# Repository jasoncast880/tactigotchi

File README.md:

🚀 Project Title

A handheld system based on the Raspberry Pi Pico W
📦 Overview

This project features:

    Custom hardware using RP2040

    Firmware written in C/C++ using GCC & Pico SDK

    Support for SPI LCD Display & SD Card, I2C Buttons, Wi-Fi, BLE, DMA Data Transfer (PIO is WIP)

🔧 Hardware
Microcontroller

    Board: [e.g., Raspberry Pi Pico / STM32F401 / ESP32]

    Processor: [e.g., ARM Cortex-M0+ @ 133MHz]

Schematic & PCB <br>
MCU Schematic:<br>
<br>
PSU:<br>
<br>
LCD/SDC THT Module:<br>
<br>
Speaker && IR Emitter Modules:<br>
<br>

    [Link to schematic or image]

    [Link to PCB files or KiCad/Altium project]

🧠 Firmware
Features

[Feature 1 – e.g., Sensor reading with ADC]

[Feature 2 – e.g., Wi-Fi transmission]

    [Planned Feature – e.g., OTA firmware update]

Toolchain

    Language: C/C++

    Build System: CMake

    RTOS: FreeRTOS

    SDK: Raspberry Pi Pico SDK v1.5.1 (update)

Directory Structure (update...)

project/
├── hardware/         # Schematics, PCB design files
├── pockpet/
└── README.md

🚀 Getting Started
Requirements

    Compiler/toolchain: arm-none-eabi-gcc

    A 'Tactigotchi' official hardware kit!

Building the Firmware

git clone https://github.com/yourusername/project.git
cd project
mkdir build && cd build
cmake ..
make

Flashing to Device

# Example for Raspberry Pi Pico (drag-and-drop)
cp firmware.uf2 /media/PI-PICO/

Or, using OpenOCD / pyOCD:

openocd -f interface/cmsis-dap.cfg -f target/rp2040.cfg

📈 Performance & Testing

    Power consumption: [value]

    Real-time responsiveness: [value / approach used]

    Debugging methods: [e.g., UART, SWD, printf-style logging]

🗂️ Documentation

    [Link to datasheets, application notes, or online documentation]

    [Optional: Link to a GitHub Wiki or Doxygen-generated docs]

🧪 Development Notes

    Known Issues: [List any bugs or limitations]

    Future Work: [Planned improvements or extensions]

    Contributions: [Mention if pull requests/issues are welcome]

📜 License

[MIT / GPL / Apache 2.0 / etc.]
🙌 Acknowledgments

    [Any libraries or codebases used]

    [Contributors, inspirations, mentors]

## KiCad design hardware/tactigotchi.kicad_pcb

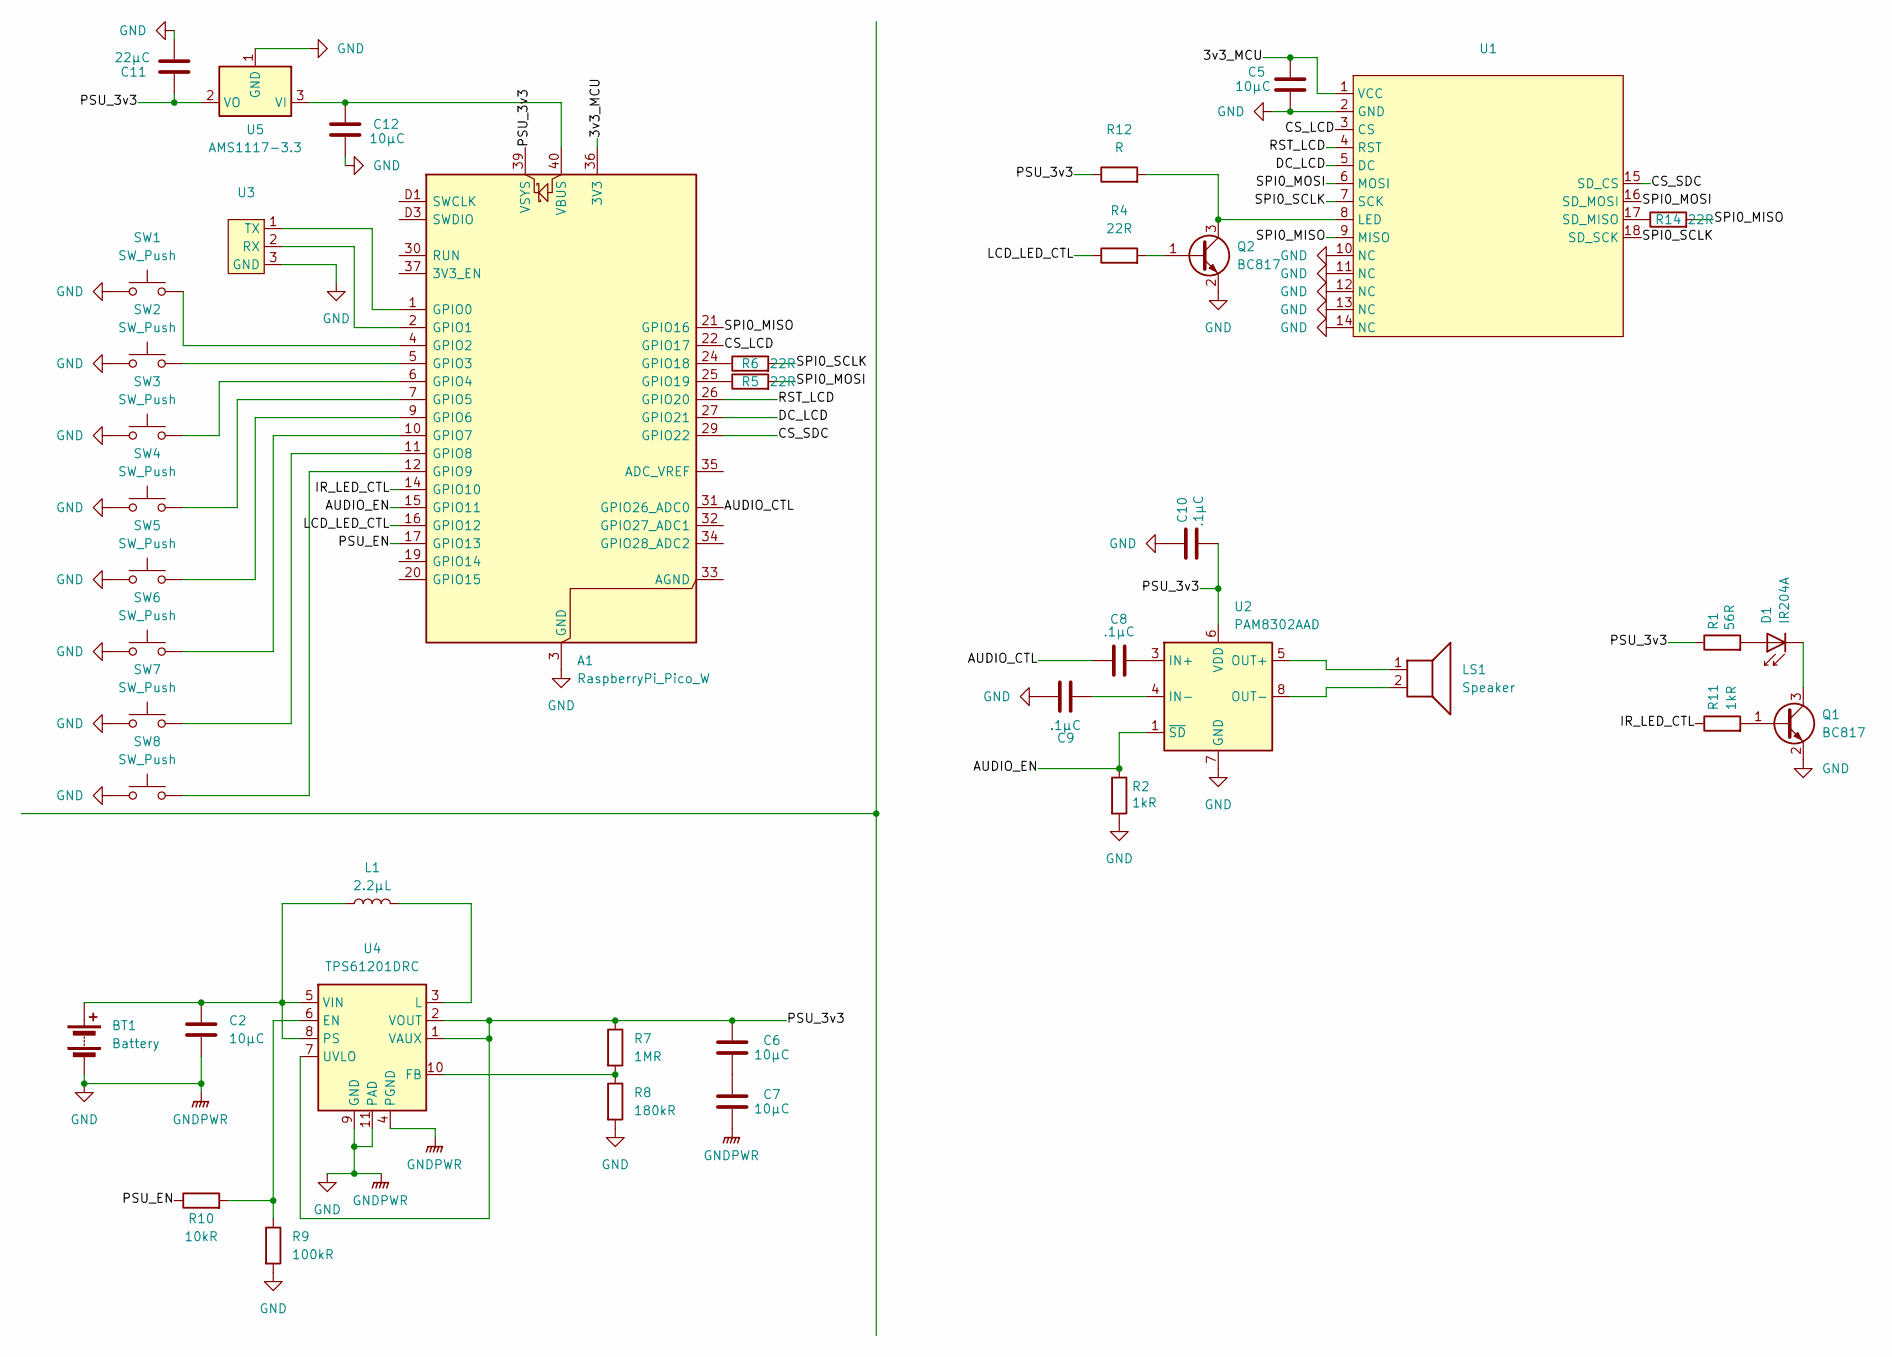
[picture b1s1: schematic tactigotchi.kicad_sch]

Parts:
A1: RaspberryPi_Pico_W; RaspberryPi_Pico_W_SMD_HandSolder
BT1: Battery; PinHeader_1x02_P1.27mm_Vertical
C2, C5, C6, C7, C12: 10μC; C_1206_3216Metric
C8, C9, C10: .1μC; C_1206_3216Metric
C11: 22μC; C_1206_3216Metric
D1: IR204A; LED_D3.0mm_IRBlack
L1: 2.2μL; L_1206_3216Metric
LS1: Speaker; Buzzer_12x9.5RM7.6
Q1, Q2: BC817; SOT-23
R1: 56R; R_1206_3216Metric
R2, R11: 1kR; R_1206_3216Metric
R4, R5, R6, R14: 22R; R_1206_3216Metric
R7: 1MR; R_1206_3216Metric
R8: 180kR; R_1206_3216Metric
R9: 100kR; R_1206_3216Metric
R10: 10kR; R_1206_3216Metric
R12: R; R_1206_3216Metric
SW1, SW2, SW3, SW4, SW5, SW6, SW7, SW8: SW_Push; SW_SPST_PTS645
U1: ILI9341_Module
U2: PAM8302AAD; SOIC-8-1EP_3.9x4.9mm_P1.27mm_EP2.41x3.3mm
U3: 3x1_PinHeader
U4: TPS61201DRC; Texas_S-PVSON-N10_ThermalVias
U5: AMS1117-3.3; SOT-223-3_TabPin2

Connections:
/3v3_MCU: A1.36 (3V3), C5.1, U1.1 (VCC)
/AUDIO_CTL: A1.31 (GPIO26_ADC0), C8.1
/AUDIO_EN: A1.15 (GPIO11), R2.1, U2.1 (~SD)
/CS_LCD: A1.22 (GPIO17), U1.3 (CS)
/CS_SDC: A1.29 (GPIO22), U1.15 (SD_CS)
/DC_LCD: A1.27 (GPIO21), U1.5 (DC)
/IR_LED_CTL: A1.14 (GPIO10), R11.1
/LCD_LED_CTL: A1.16 (GPIO12), R4.1
/PSU_3v3: A1.39 (VSYS), C6.2, C10.2, C11.1, R1.1, R7.1, R12.1, U2.6 (VDD), U4.1 (VAUX), U4.2 (VOUT), U4.7 (UVLO), U5.2 (VO)
/PSU_EN: A1.17 (GPIO13), R10.1
/RST_LCD: A1.26 (GPIO20), U1.4 (RST)
/SPI0_MISO: A1.21 (GPIO16), R14.2, U1.9 (MISO)
/SPI0_MOSI: R5.2, U1.6 (MOSI), U1.16 (SD_MOSI)
/SPI0_SCLK: R6.2, U1.7 (SCK), U1.18 (SD_SCK)
GND: A1.3 (GND), A1.8 (GND), A1.13 (GND), A1.18 (GND), A1.23 (GND), A1.28 (GND), A1.38 (GND), A1.D2 (GND), BT1.2 (-), C2.2, C5.2, C7.1, C9.2, C10.1, C11.2, C12.2, Q1.2 (E), Q2.2 (E), R2.2, R8.2, R9.2, SW1.1, SW2.1, SW3.1, SW4.1, SW5.1, SW6.1, SW7.1, SW8.1, U1.2 (GND), U1.10 (NC), U1.11 (NC), U1.12 (NC), U1.13 (NC), U1.14 (NC), U2.7 (GND), U3.3 (GND), U4.4 (PGND), U4.9 (GND), U4.11 (PAD), U5.1 (GND)
unnamed: A1.1 (GPIO0), U3.1 (TX)
unnamed: A1.2 (GPIO1), U3.2 (RX)
unnamed: A1.4 (GPIO2), SW1.2
unnamed: A1.5 (GPIO3), SW2.2
unnamed: A1.6 (GPIO4), SW3.2
unnamed: A1.7 (GPIO5), SW4.2
unnamed: A1.9 (GPIO6), SW5.2
unnamed: A1.10 (GPIO7), SW6.2
unnamed: A1.11 (GPIO8), SW7.2
unnamed: A1.12 (GPIO9), SW8.2
unnamed: A1.24 (GPIO18), R6.1
unnamed: A1.25 (GPIO19), R5.1
unnamed: A1.40 (VBUS), C12.1, U5.3 (VI)
unnamed: BT1.1 (+), C2.1, L1.1, U4.5 (VIN), U4.8 (PS)
unnamed: C6.1, C7.2
unnamed: D1.2 (A), R1.2
unnamed: D1.1 (K), Q1.3 (C)
unnamed: Q1.1 (B), R11.2
unnamed: Q2.1 (B), R4.2
unnamed: Q2.3 (C), R12.2, U1.8 (LED)
unnamed: R14.1, U1.17 (SD_MISO)
unnamed: C8.2, U2.3 (IN+)
unnamed: C9.1, U2.4 (IN-)
unnamed: LS1.1, U2.5 (OUT+)
unnamed: LS1.2, U2.8 (OUT-)
unnamed: R9.1, R10.2, U4.6 (EN)
unnamed: R7.2, R8.1, U4.10 (FB)
unnamed: L1.2, U4.3 (L)

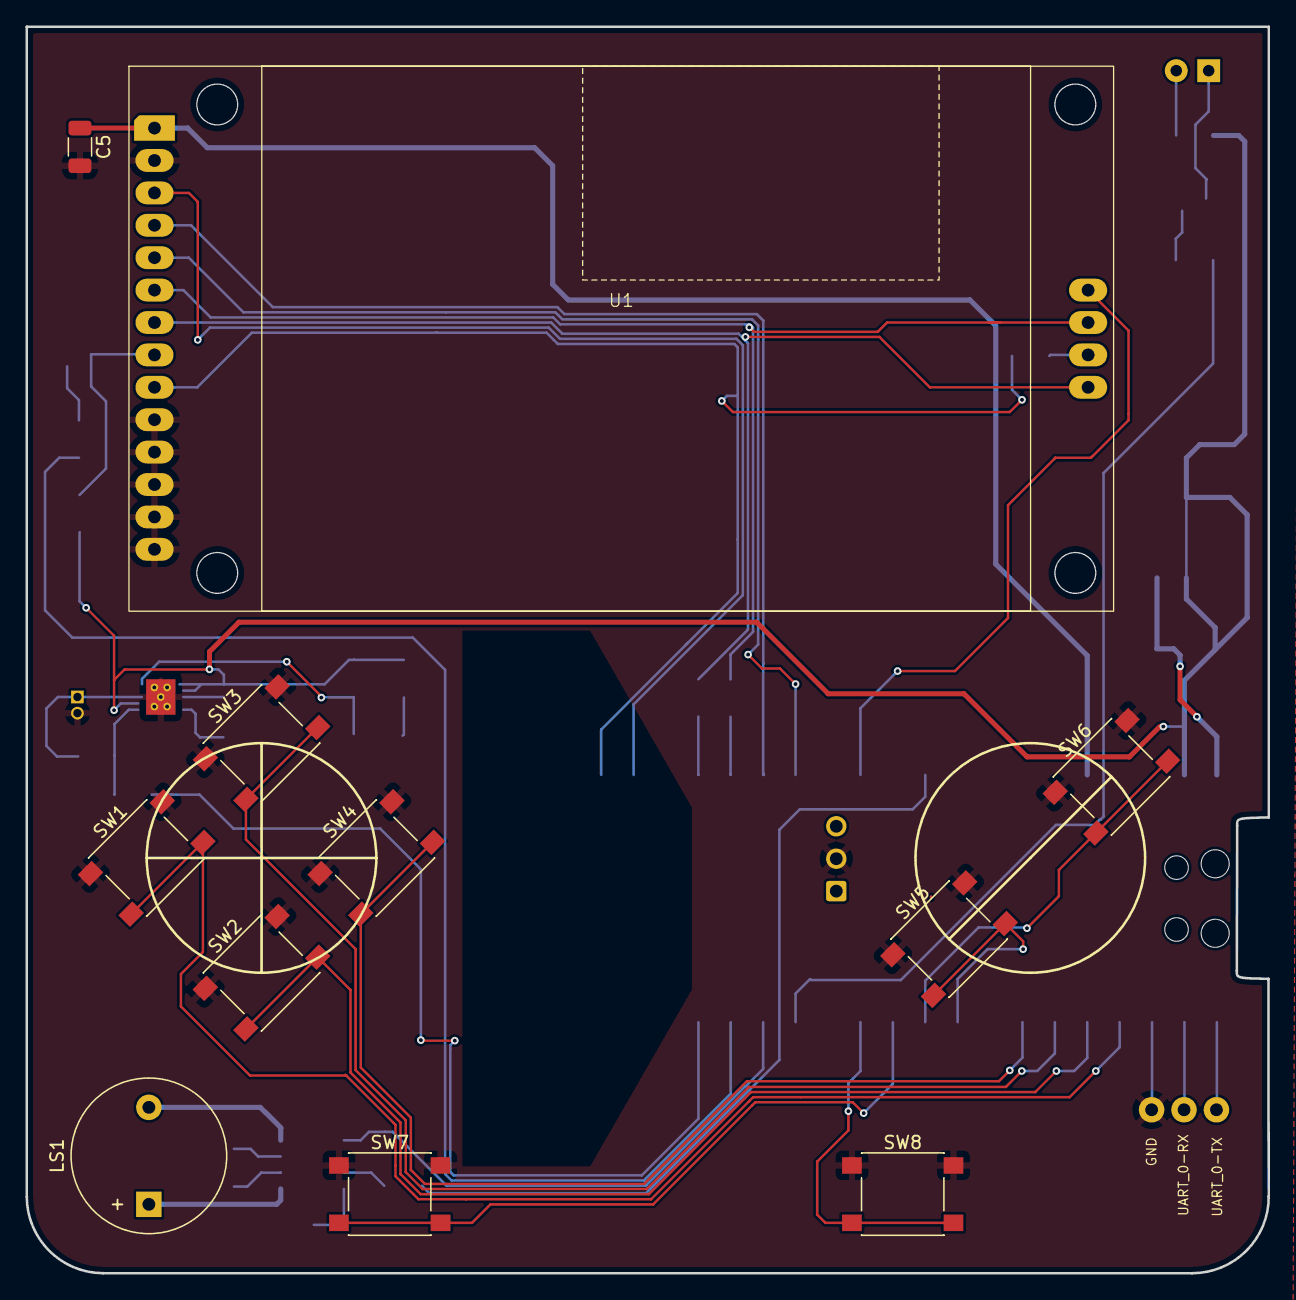
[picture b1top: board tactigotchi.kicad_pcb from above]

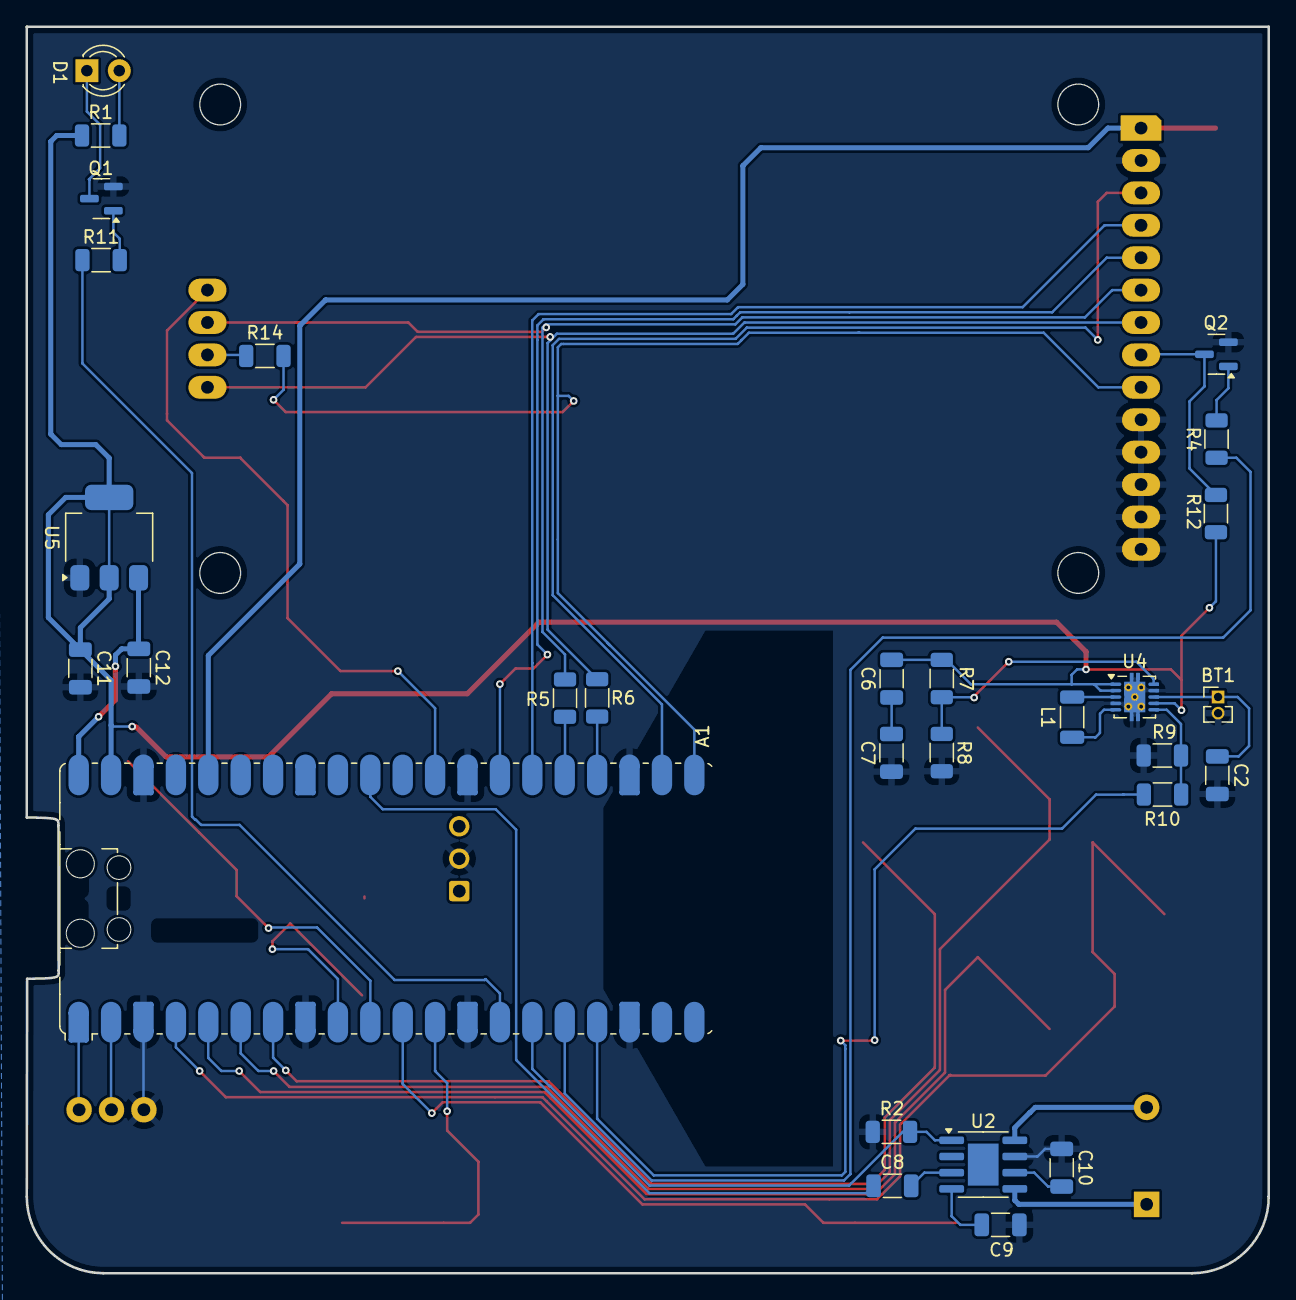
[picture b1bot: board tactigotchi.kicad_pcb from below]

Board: 2 copper layers, 97.4 x 97.7 mm, 41 parts (29 on the bottom side), 43 nets.

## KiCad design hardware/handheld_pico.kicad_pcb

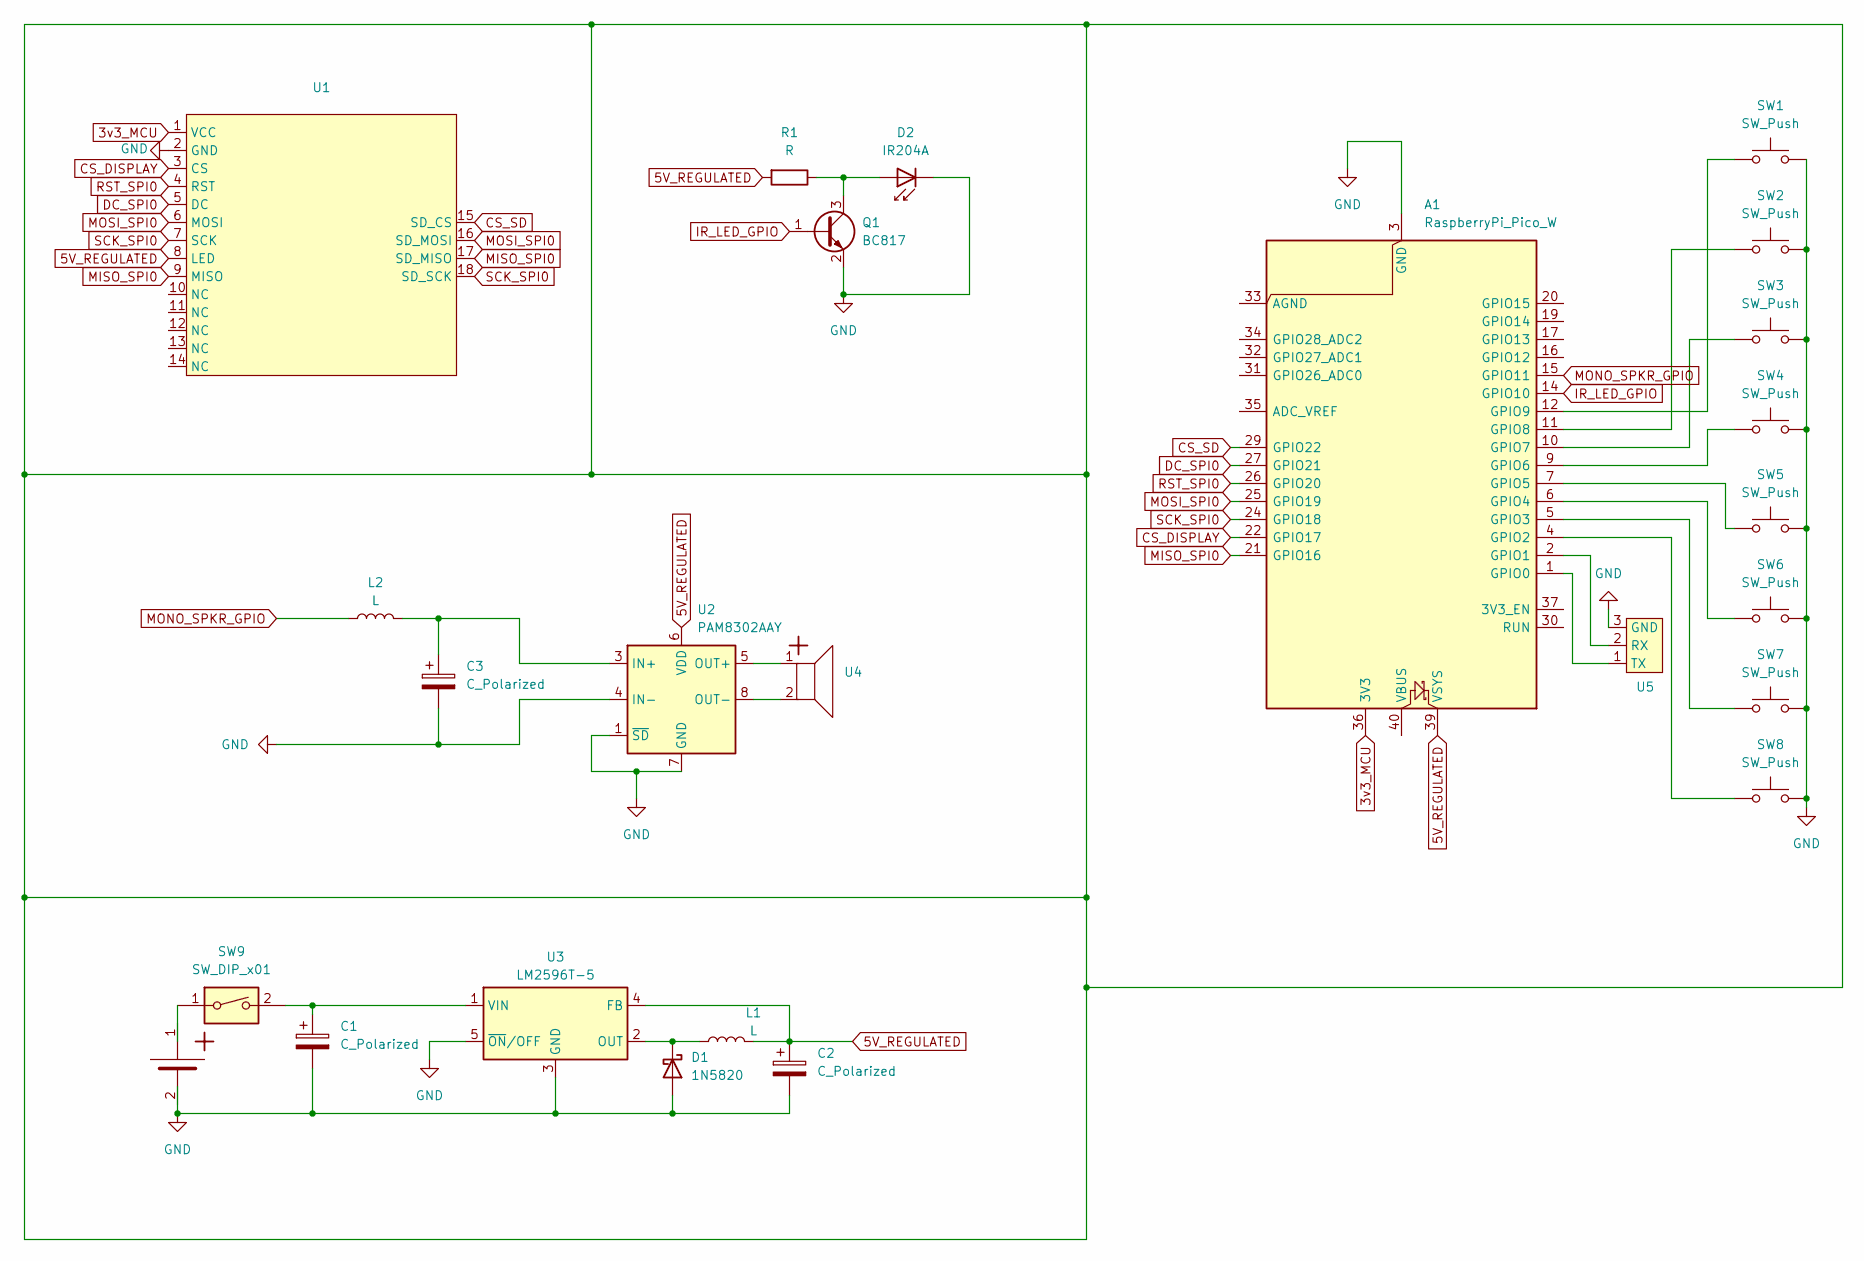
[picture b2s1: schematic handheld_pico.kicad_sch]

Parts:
A1: RaspberryPi_Pico_W; RaspberryPi_Pico_Common_SMD
B1: Terminal_THT
C1, C2, C3: C_Polarized; C_1210_3225Metric_Pad1.33x2.70mm_HandSolder
D1: 1N5820; D_DO-201AD_P15.24mm_Horizontal
D2: IR204A; LED_D3.0mm_IRBlack
L1, L2: L; L_1210_3225Metric_Pad1.42x2.65mm_HandSolder
Q1: BC817; SOT-23
R1: R; R_1206_3216Metric_Pad1.30x1.75mm_HandSolder
SW1, SW2, SW3, SW4, SW5, SW6, SW7, SW8: SW_Push; SW_PUSH_6mm
SW9: SW_DIP_x01; SW_DIP_SPSTx01_Slide_6.7x4.1mm_W7.62mm_P2.54mm_LowProfile
U1: ILI9341_Module
U2: PAM8302AAY; DFN-8-1EP_3x3mm_P0.65mm_EP1.55x2.4mm
U3: LM2596T-5; TO-220-5_P3.4x3.7mm_StaggerOdd_Lead3.8mm_Vertical
U4: Terminal_THT
U5: 3x1_PinHeader

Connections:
3v3_MCU: A1.36 (3V3), U1.1 (VCC)
5V_REGULATED: A1.39 (VSYS), C2.1, L1.2, R1.2, U1.8 (LED), U2.6 (VDD), U3.4 (FB)
CS_DISPLAY: A1.22 (GPIO17), U1.3 (CS)
CS_SD: A1.29 (GPIO22), U1.15 (SD_CS)
DC_SPI0: A1.27 (GPIO21), U1.5 (DC)
GND: A1.3 (GND), A1.8 (GND), A1.13 (GND), A1.18 (GND), A1.23 (GND), A1.28 (GND), A1.38 (GND), B1.2, C1.2, C2.2, C3.2, D1.2 (A), D2.1 (K), Q1.2 (E), SW1.2, SW2.2, SW3.2, SW4.2, SW5.2, SW6.2, SW7.2, SW8.2, U1.2 (GND), U2.1 (~SD), U2.4 (IN-), U2.7 (GND), U3.3 (GND), U3.5 (~ON/OFF), U5.3 (GND)
IR_LED_GPIO: A1.14 (GPIO10), Q1.1 (B)
MISO_SPI0: A1.21 (GPIO16), U1.9 (MISO), U1.17 (SD_MISO)
MONO_SPKR_GPIO: A1.15 (GPIO11), L2.1
MOSI_SPI0: A1.25 (GPIO19), U1.6 (MOSI), U1.16 (SD_MOSI)
unnamed: A1.1 (GPIO0), U5.1 (TX)
unnamed: A1.2 (GPIO1), U5.2 (RX)
unnamed: A1.4 (GPIO2), SW8.1
unnamed: A1.5 (GPIO3), SW7.1
unnamed: A1.6 (GPIO4), SW6.1
unnamed: A1.7 (GPIO5), SW5.1
unnamed: A1.9 (GPIO6), SW4.1
unnamed: A1.10 (GPIO7), SW3.1
unnamed: A1.11 (GPIO8), SW2.1
unnamed: A1.12 (GPIO9), SW1.1
unnamed: B1.1, SW9.1
unnamed: D1.1 (K), L1.1, U3.2 (OUT)
unnamed: D2.2 (A), Q1.3 (C), R1.1
unnamed: C3.1, L2.2, U2.3 (IN+)
unnamed: U2.5 (OUT+), U4.1
unnamed: U2.8 (OUT-), U4.2
unnamed: C1.1, SW9.2, U3.1 (VIN)
RST_SPI0: A1.26 (GPIO20), U1.4 (RST)
SCK_SPI0: A1.24 (GPIO18), U1.7 (SCK), U1.18 (SD_SCK)

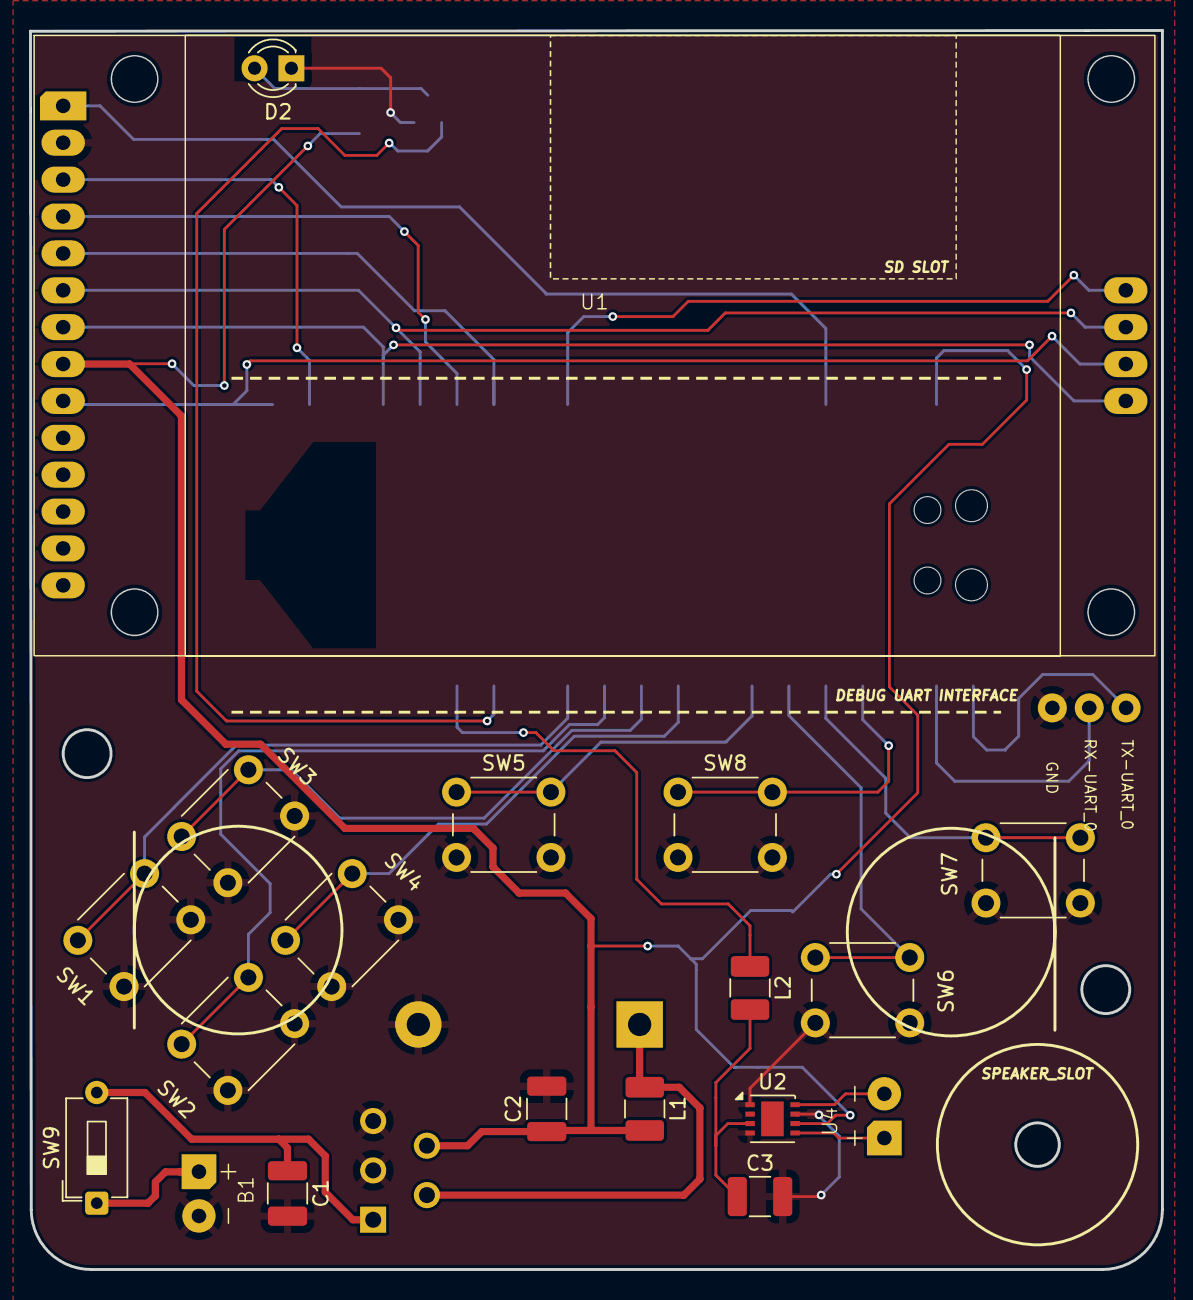
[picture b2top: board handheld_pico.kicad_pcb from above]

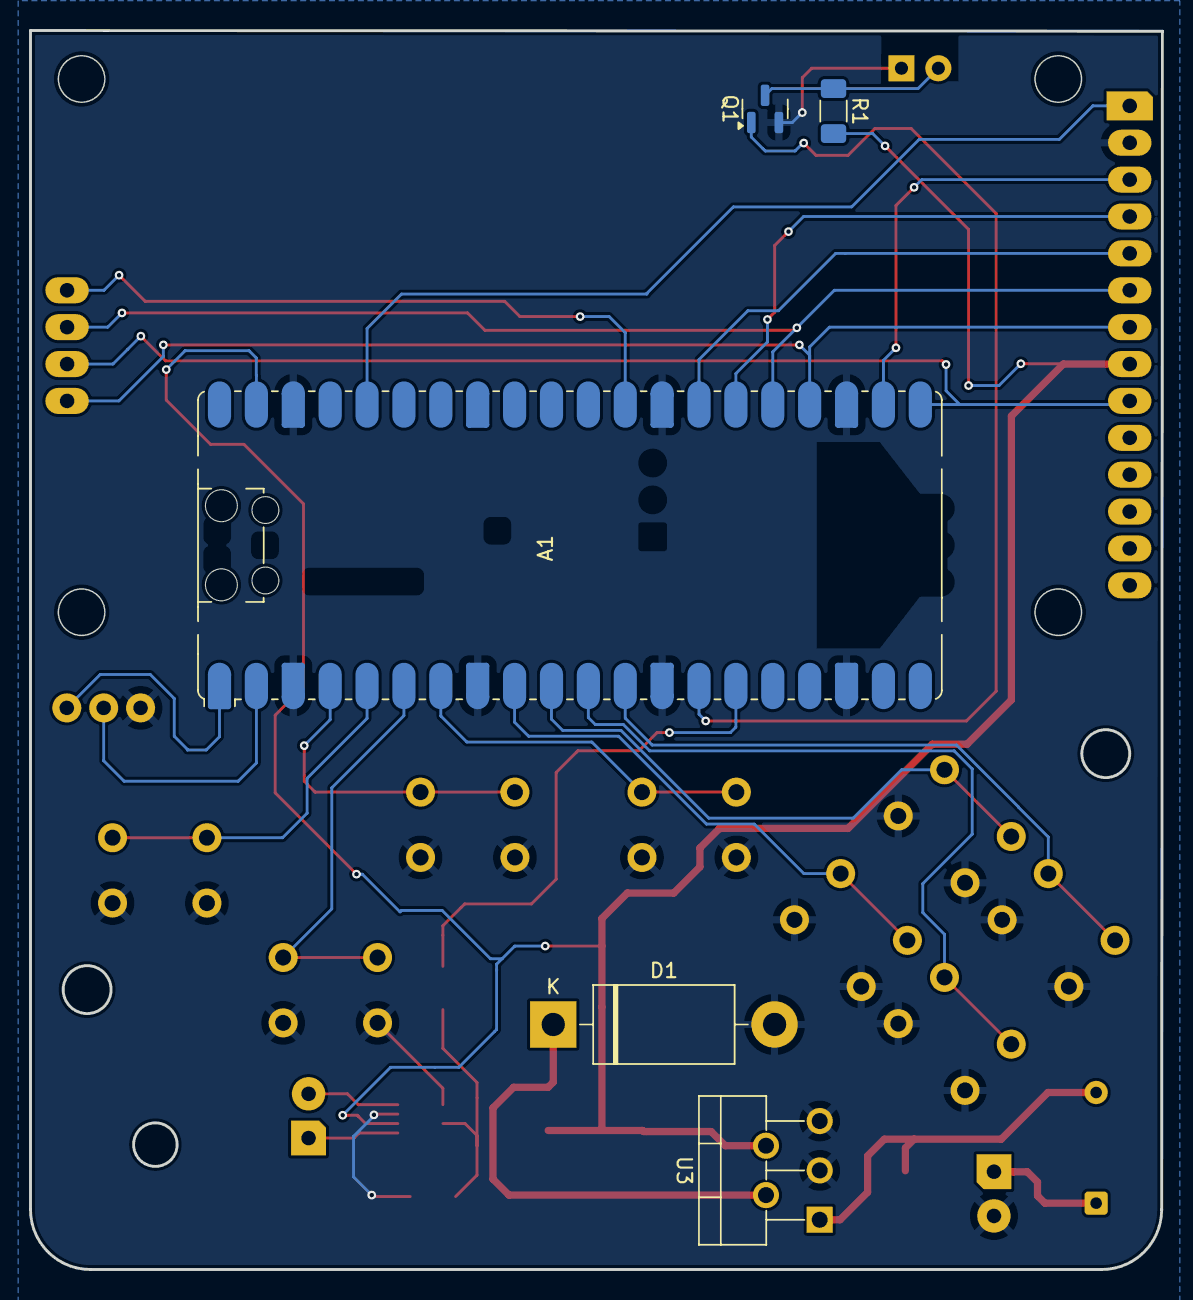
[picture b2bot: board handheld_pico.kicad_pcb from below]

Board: 2 copper layers, 78.0 x 85.3 mm, 25 parts (5 on the bottom side), 29 nets.

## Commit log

2025-04-21 Add files via upload
    handheld_pico project files.
2025-04-24 HW v.0.1: no layout, all tht components
2025-04-26 Add files via upload
    smd schematic drop-in replacements, changes to psu module
2025-04-26 beginnings of pcb layout
2025-04-28 v1.0, prod ready(?)
